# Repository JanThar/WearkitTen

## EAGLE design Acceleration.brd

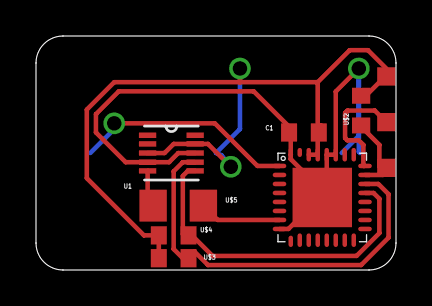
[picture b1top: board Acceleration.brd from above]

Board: 2 copper layers, 20.0 x 13.0 mm, 8 parts (0 on the bottom side), 9 nets.

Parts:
C1: 100n; 603
U1: MMA7660FCT; DFN300X300X100-10N
U$1: CARRIER_SMD2SMD2_3POL; CARRIER_SMD2_3POL
U$2: 10k; 603
U$3, U$4: 4.7k; 603
U$5: 0; 1206
U$10: MSP430G2553; QFN32

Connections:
GND: C1.2, U1.4, U1.8, U$1.GND, U$10.8, U$10.27, U$10.28, U$10.32, U$10.TP
unnamed: U1.6, U$4.2, U$10.21
unnamed: U$1.TST, U$10.24
unnamed: U$1.RST, U$2.1, U$10.23
unnamed: U1.7, U$3.1, U$10.22
unnamed: U$5.2, U$10.7
unnamed: U1.5, U$5.1
unnamed: U$1.RX/TX, U$10.1
VCC: C1.1, U1.3, U1.9, U$1.VCC, U$1.VCC'', U$2.2, U$3.2, U$4.1, U$10.29, U$10.30

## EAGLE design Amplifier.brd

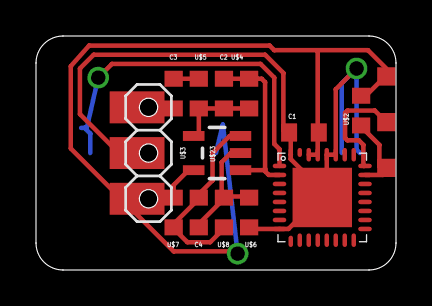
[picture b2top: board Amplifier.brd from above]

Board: 2 copper layers, 20.0 x 13.0 mm, 14 parts (0 on the bottom side), 11 nets.

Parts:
C1: 100n; 603
C2: 100p; 603
C3, C4: 1µ; 603
U$1: CARRIER_SMD2SMD2_3POL; CARRIER_SMD2_3POL
U$2, U$7, U$8: 10k; 603
U$3: PINHD_32.54MOD; PINHD_3_MOD
U$4: 100k; 603
U$5: 1.5k; 603
U$6: 2k; 603
U$10: MSP430G2553; QFN32
U$23: OPA344; SOT23-5

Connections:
GND: C1.2, U$1.GND, U$3.P$2, U$6.2, U$10.8, U$10.27, U$10.28, U$10.32, U$10.TP
unnamed: U$1.TST, U$10.24
unnamed: U$1.RST, U$2.1, U$10.23
unnamed: U$1.RX/TX, U$10.1
unnamed: C2.1, U$4.1, U$5.2, U$23.4
unnamed: C3.2, U$5.1
unnamed: C4.1, U$6.1, U$8.1, U$23.2
unnamed: C3.1, U$3.P$1
unnamed: C4.2, U$7.2, U$8.2, U$23.3
SOUND: C2.2, U$4.2, U$10.2, U$23.1
VCC: C1.1, U$1.VCC, U$1.VCC'', U$2.2, U$3.P$3, U$7.1, U$10.29, U$10.30, U$23.5

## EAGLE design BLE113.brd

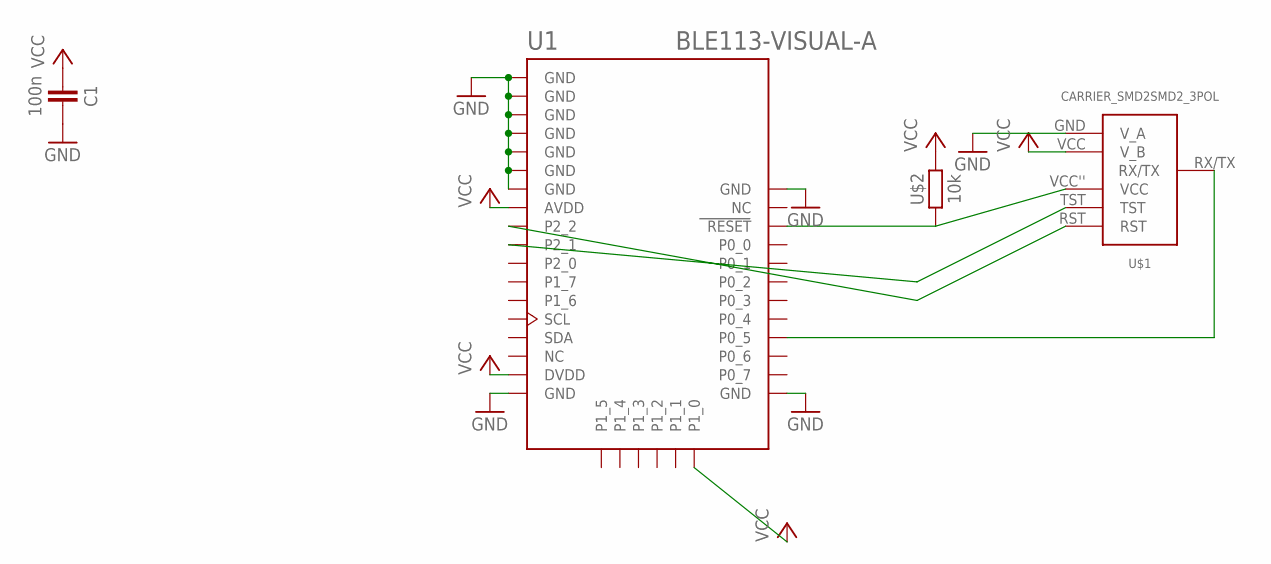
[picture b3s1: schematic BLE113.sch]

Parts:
C1: 100n; 603
U1: BLE113-VISUAL-A; BLE113-A
U$1: CARRIER_SMD2SMD2_3POL; CARRIER_SMD2_3POL
U$2: 10k; 603

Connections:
GND: C1.2, U1.GND, U1.GND@2 (GND), U1.GND@3 (GND), U1.GND@4 (GND), U1.GND@5 (GND), U1.GND@6 (GND), U1.GND@7 (GND), U1.GND@8 (GND), U1.GND@9 (GND), U1.GND@10 (GND), U$1.GND (V_A)
unnamed: U1.RESET, U$1.VCC'' (VCC), U$2.1
unnamed: U1.P2_2, U$1.RST
unnamed: U1.P2_1, U$1.TST
unnamed: U1.P0_5, U$1.RX/TX
VCC: C1.1, U1.AVDD, U1.DVDD, U1.P1_0, U$1.VCC (V_B), U$2.2

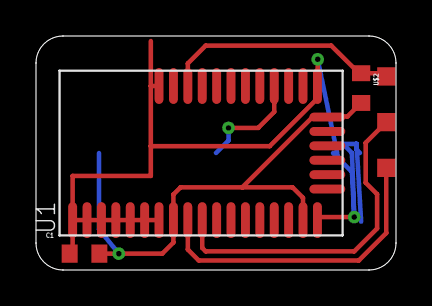
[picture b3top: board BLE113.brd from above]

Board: 2 copper layers, 20.0 x 13.0 mm, 4 parts (0 on the bottom side), 6 nets.

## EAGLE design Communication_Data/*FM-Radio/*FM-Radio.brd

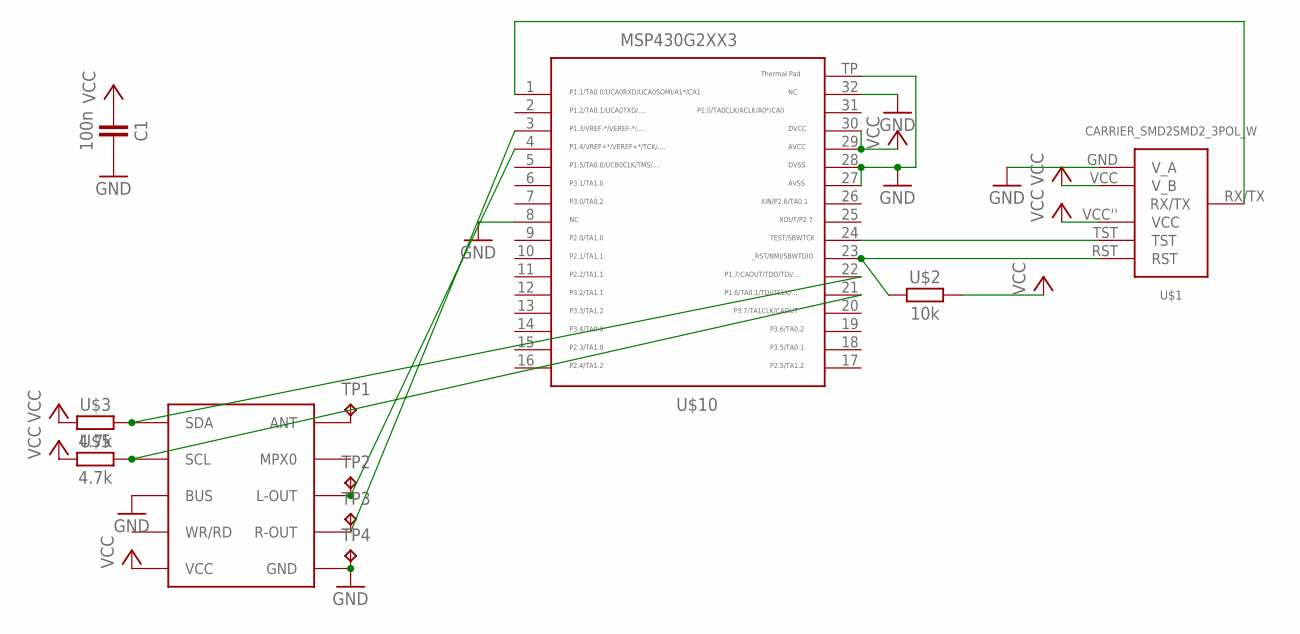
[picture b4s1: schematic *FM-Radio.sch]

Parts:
C1: 100n; 603
TP1, TP2, TP3, TP4: TPTP06R; TP06R
U$1: CARRIER_SMD2SMD2_3POL_W; CARRIER_SMD2_WIDE_3POL
U$2: 10k; 603
U$3, U$5: 4.7k; 603
U$4: FM-RADIO
U$10: MSP430G2553; QFN32

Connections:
GND: C1.2, TP4.TP, U$1.GND (V_A), U$4.PAD3 (BUS), U$4.PAD6 (GND), U$10.8, U$10.27, U$10.28, U$10.32, U$10.TP
unnamed: TP2.TP, U$4.PAD9 (L-OUT), U$10.4
unnamed: U$1.TST, U$10.24
unnamed: U$1.RST, U$2.1, U$10.23
unnamed: TP3.TP, U$4.PAD7 (R-OUT), U$10.3
unnamed: TP1.TP, U$4.PAD11 (ANT)
unnamed: U$3.2, U$4.PAD1 (SDA), U$10.22
unnamed: U$4.PAD2 (SCL), U$5.2, U$10.21
unnamed: U$1.RX/TX, U$10.1
VCC: C1.1, U$1.VCC (V_B), U$1.VCC'' (VCC), U$2.2, U$3.1, U$4.PAD5 (VCC), U$5.1, U$10.29, U$10.30

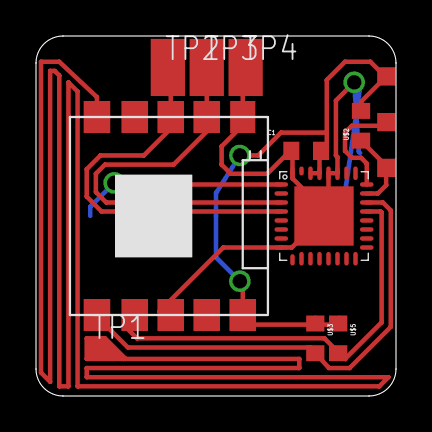
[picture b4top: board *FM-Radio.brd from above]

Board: 2 copper layers, 20.0 x 20.0 mm, 11 parts (0 on the bottom side), 10 nets.

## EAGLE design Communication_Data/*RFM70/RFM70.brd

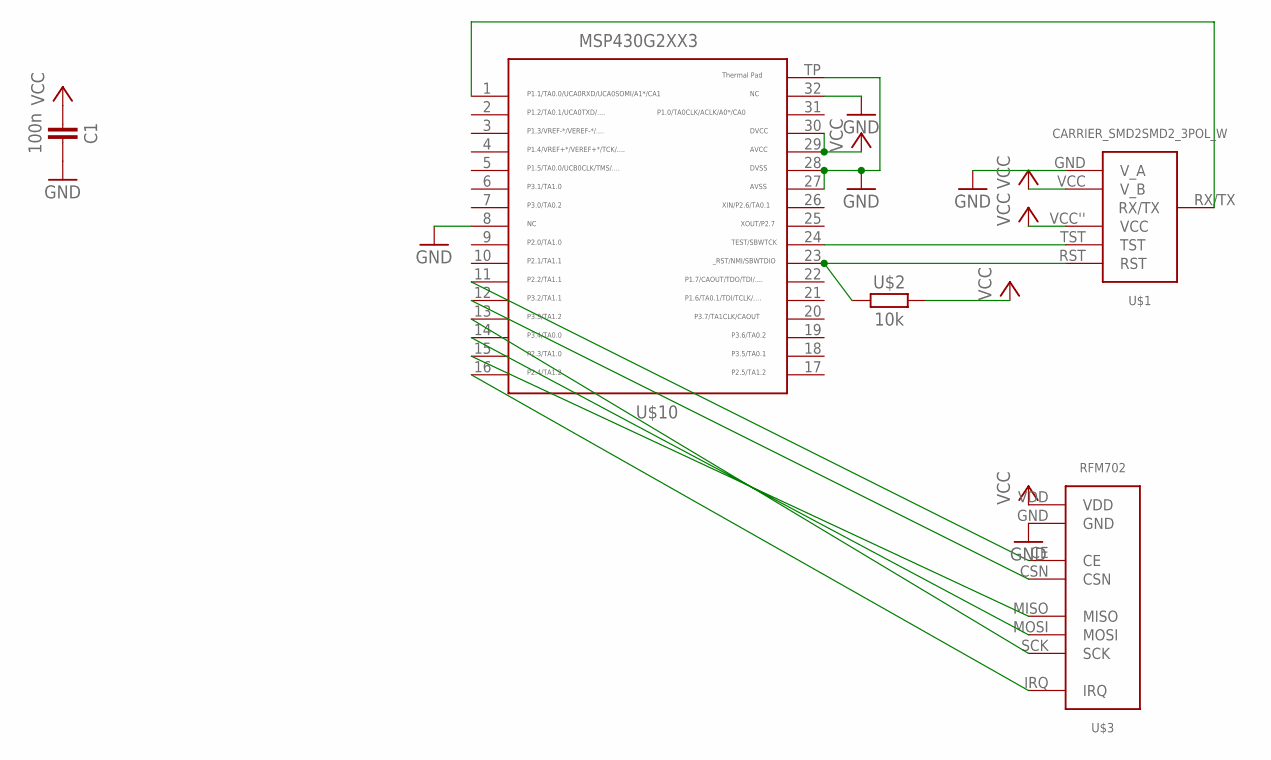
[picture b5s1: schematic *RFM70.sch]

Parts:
C1: 100n; 603
U$1: CARRIER_SMD2SMD2_3POL_W; CARRIER_SMD2_WIDE_3POL
U$2: 10k; 603
U$3: RFM702; RFM70_SMD
U$10: MSP430G2553; QFN32

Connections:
GND: C1.2, U$1.GND (V_A), U$3.GND, U$10.8, U$10.27, U$10.28, U$10.32, U$10.TP
unnamed: U$3.IRQ, U$10.16
unnamed: U$1.TST, U$10.24
unnamed: U$1.RST, U$2.1, U$10.23
unnamed: U$3.MISO, U$10.15
unnamed: U$3.MOSI, U$10.14
unnamed: U$3.SCK, U$10.13
unnamed: U$3.CSN, U$10.12
unnamed: U$1.RX/TX, U$10.1
unnamed: U$3.CE, U$10.11
VCC: C1.1, U$1.VCC (V_B), U$1.VCC'' (VCC), U$2.2, U$3.VDD, U$10.29, U$10.30

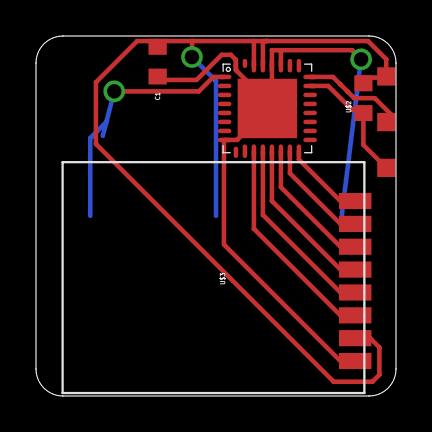
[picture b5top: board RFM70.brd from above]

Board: 2 copper layers, 20.0 x 20.0 mm, 5 parts (0 on the bottom side), 11 nets.

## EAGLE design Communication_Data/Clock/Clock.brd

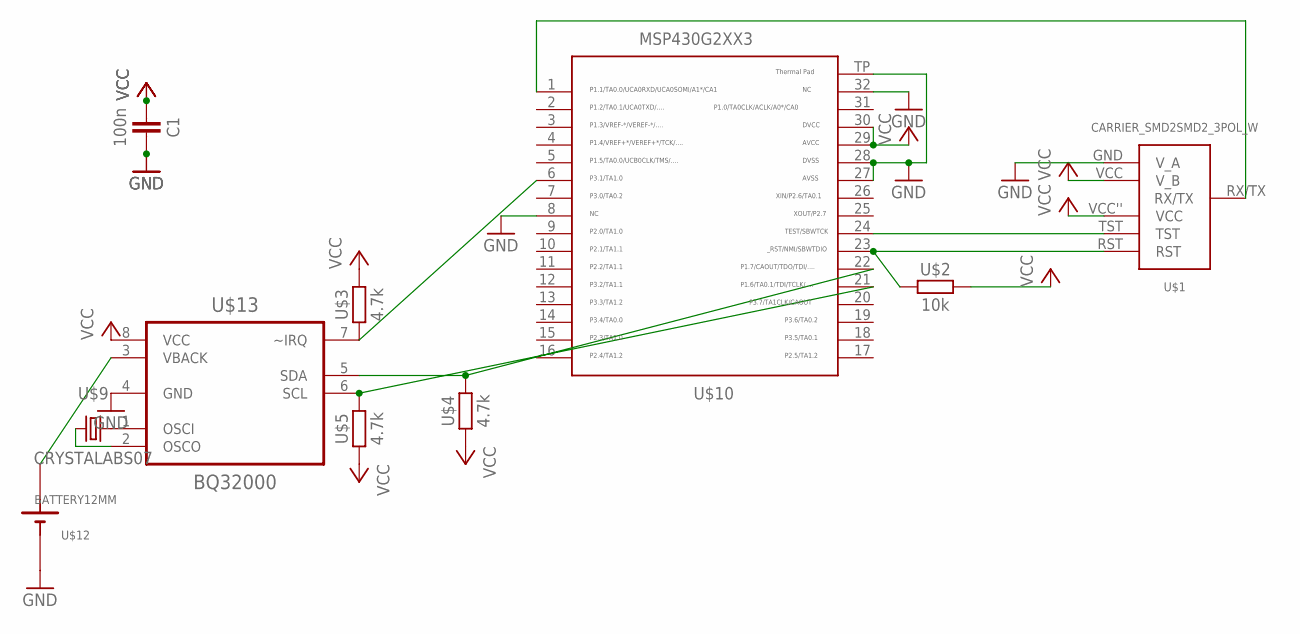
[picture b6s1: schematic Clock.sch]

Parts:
C1: 100n; 603
U$1: CARRIER_SMD2SMD2_3POL_W; CARRIER_SMD2_WIDE_3POL
U$2: 10k; 603
U$3, U$4, U$5: 4.7k; 603
U$9: CRYSTALABS07; ABS07
U$10: MSP430G2553; QFN32
U$12: BATTERY12MM; BATTERY-12MM
U$13: BQ32000; SOIC8

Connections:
GND: C1.2, U$1.GND (V_A), U$10.8, U$10.27, U$10.28, U$10.32, U$10.TP, U$12.GND (-), U$13.4 (GND)
unnamed: U$5.2, U$10.21, U$13.6 (SCL)
unnamed: U$1.TST, U$10.24
unnamed: U$1.RST, U$2.1, U$10.23
unnamed: U$4.2, U$10.22, U$13.5 (SDA)
unnamed: U$3.1, U$10.6, U$13.7 (~IRQ)
unnamed: U$1.RX/TX, U$10.1
unnamed: U$9.1, U$13.2 (OSCO)
unnamed: U$9.2, U$13.1 (OSCI)
unnamed: U$12.PWR@1 (+), U$12.PWR@2 (+), U$13.3 (VBACK)
VCC: C1.1, U$1.VCC (V_B), U$1.VCC'' (VCC), U$2.2, U$3.2, U$4.1, U$5.1, U$10.29, U$10.30, U$13.8 (VCC)

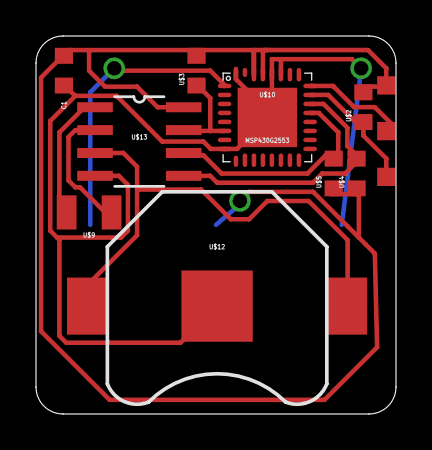
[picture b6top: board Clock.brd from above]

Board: 2 copper layers, 20.0 x 21.0 mm, 10 parts (0 on the bottom side), 11 nets.

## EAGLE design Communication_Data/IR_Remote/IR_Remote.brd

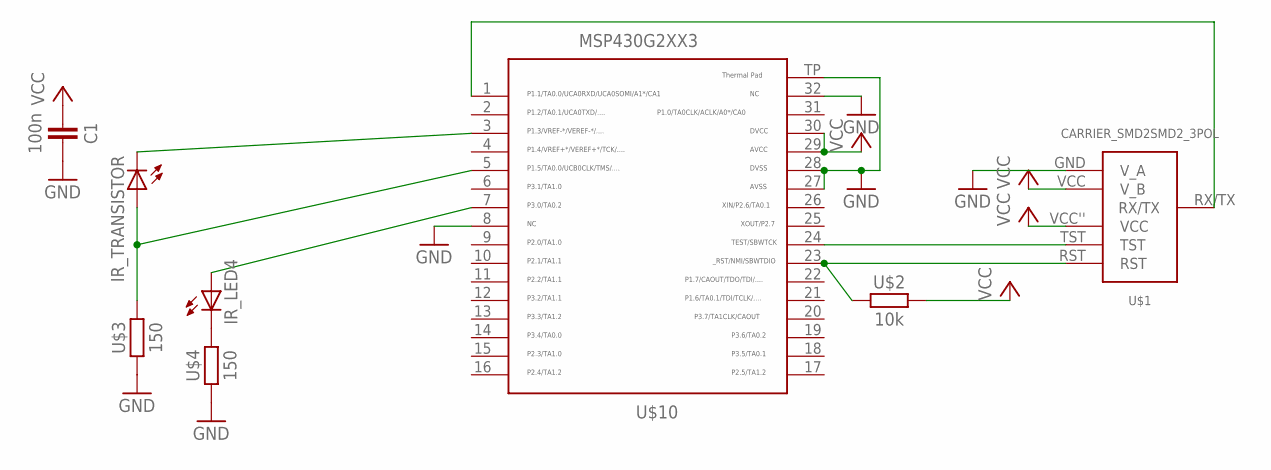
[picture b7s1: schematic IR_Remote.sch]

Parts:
C1: 100n; 603
IR_LED4: LEDCHIP-LED0603; CHIP-LED0603
IR_TRANSISTOR: LEDCHIP-LED0603; CHIP-LED0603
U$1: CARRIER_SMD2SMD2_3POL; CARRIER_SMD2_3POL
U$2: 10k; 603
U$3, U$4: 150; 603
U$10: MSP430G2553; QFN32

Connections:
GND: C1.2, U$1.GND (V_A), U$3.1, U$4.1, U$10.8, U$10.27, U$10.28, U$10.32, U$10.TP
unnamed: IR_LED4.C, U$4.2
unnamed: U$1.TST, U$10.24
unnamed: U$1.RST, U$2.1, U$10.23
unnamed: IR_TRANSISTOR.A, U$3.2, U$10.5
unnamed: U$1.RX/TX, U$10.1
unnamed: IR_LED4.A, U$10.7
unnamed: IR_TRANSISTOR.C, U$10.3
VCC: C1.1, U$1.VCC (V_B), U$1.VCC'' (VCC), U$2.2, U$10.29, U$10.30

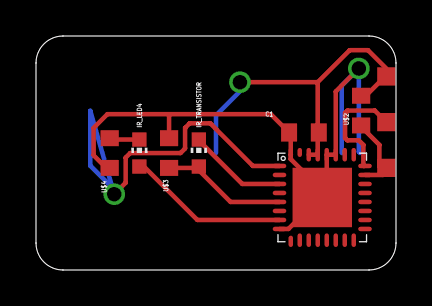
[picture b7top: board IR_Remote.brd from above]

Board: 2 copper layers, 20.0 x 13.0 mm, 8 parts (0 on the bottom side), 9 nets.

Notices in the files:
parts and their libraries:
SparkFun-AnalogIC: Licensing: CC v3.0 Share-Alike You are welcome to use this library for commercial purposes.
